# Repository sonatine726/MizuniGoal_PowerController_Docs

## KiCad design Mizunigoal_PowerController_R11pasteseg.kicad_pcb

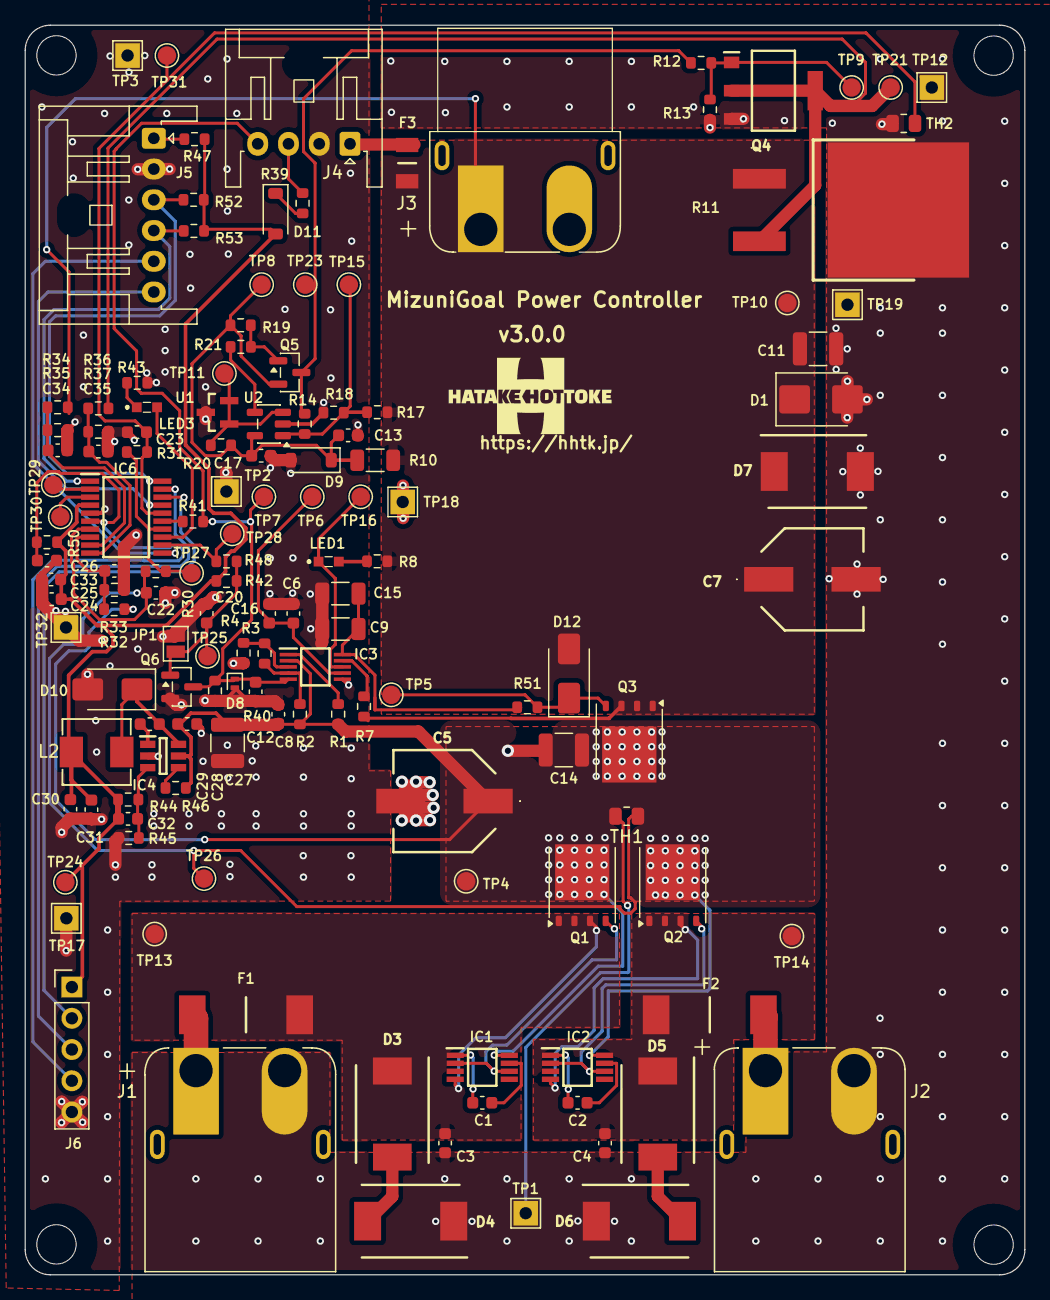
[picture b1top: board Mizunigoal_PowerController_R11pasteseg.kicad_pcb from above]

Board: 2 copper layers, 81.3 x 101.6 mm, 142 parts (0 on the bottom side), 62 nets.

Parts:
C1, C2, C13, C17, C24: 1µF; C_0603_1608Metric
C3, C4: 100pF(C0G/100V); C_0603_1608Metric
C5, C7: 47uF(EEH-ZC1H470P); EEHZA1H680P
C6: 0.33uF; C_0603_1608Metric
C8, C28: 100nF(100V); C_0603_1608Metric
C9, C15: 22nF(C0G/100V/1206); C_1206_3216Metric
C11: 1uF(100V/1210); C_1210_3225Metric
C12, C20, C25, C26, C29, C31, C33: 100nF; C_0603_1608Metric
C14: 4.7µF(100V/1210); C_1210_3225Metric
C16: 0.15uF; C_0603_1608Metric
C22, C23: 10nF; C_0603_1608Metric
C27: 2.2µF(100V/1210); C_1210_3225Metric
C30: 22µF(16V); C_0603_1608Metric
C32: 22pF; C_0603_1608Metric
C34, C35: 1nF(C0G); C_0603_1608Metric
D1: ES2D; D_SMB
D3, D5, D7: SMCJ33A; DIOM7959X262N
D4, D6: SMCJ6.0A; DIOM7959X262N
D8: ESD(5V); D_SOD-882
D9: BZT52C12(12V); D_SOD-123
D10: SS210(100V); D_SMA
D11: BAT46W; D_SOD-123
D12: SMAJ15A; D_SMA
F1, F2: 0456030.ER; FUSC10130X305N
F3: 1206L010_60; FUSC3216X125N
H2, H2#2, H2#3, H2#4: MountingHole_3.2mm_M3_with_safearea
IC1, IC2: LM74610QDGKRQ1; SOP65P490X110-8N
IC3: LM5060MM; SOP50P490X110-10N
IC4: LMR16006XDDCR; SOT95P280X110-6N
IC6: STM32C011F4P6; SOP65P640X120-20N
J1: Conn_01x02_Pin; XT60PW-M-Wide
J2: Conn_01x02_Pin; XT60PW-M-Wide_mod_2
J3: Conn_01x02_Pin; XT60PW-F-Wide
J4: Conn_01x04_Pin; JST_XA_S04B-XASK-1_1x04_P2.50mm_Horizontal
J5: Conn_01x06_Pin; JST_XA_S06B-XASK-1_1x06_P2.50mm_Horizontal
J6: Conn_01x05_Pin; PinHeader_1x05_P2.54mm_Vertical
JP1: Jumper_2_Open; SolderJumper-2_P1.3mm_Open_Pad1.0x1.5mm
L2: 33μH; IND-SMD_L5.4-W5.2
LED1, LED3: SML-D13FWT86; SMLD15YWT86
Q1, Q2, Q3: CSD18540Q5B; TDSON-8-1
Q4: FDT3612; SOT230P700X180-4N
Q5: MMBT3906; SOT-23
Q6: BSS138; SOT-23
R1, R12, R18, R19, R41, R50: 10kΩ; R_0603_1608Metric
R2: 200kΩ; R_0603_1608Metric
R3: 5.76kΩ; R_0603_1608Metric
R4: 13.3kΩ; R_0603_1608Metric
R7: 1kΩ; R_0603_1608Metric
R8: 27kΩ; R_0603_1608Metric
R10: 3.3kΩ(1206); R_1206_3216Metric
R11: TPAN0263F200RK9(200Ω); D2PAK_L10.1-W7.8-P5.08-LS15.3
R13, R33, R35, R37, R44, R46: 100kΩ; R_0603_1608Metric
R14, R32, R34, R36, R42: 1MΩ; R_0603_1608Metric
R17: 118kΩ; R_0603_1608Metric
R20: 6.8kΩ; R_0603_1608Metric
R21: 22kΩ; R_0603_1608Metric
R30, R31: 2.0kΩ; R_0603_1608Metric
R39, R48: 220Ω; R_0603_1608Metric
R40, R52, R53: 2.2kΩ; R_0603_1608Metric
R43: 470Ω; R_0603_1608Metric
R45: 30.1kΩ; R_0603_1608Metric
R47: 0Ω; R_0603_1608Metric
R51: 100Ω; R_0603_1608Metric
TH1, TH2: NCP21XV103J03RA(10kΩ); R_0805_2012Metric
TP1, TP2, TP3, TP12, TP17, TP18, TP19, TP32: GND; TestPoint_THTPad_2.0x2.0mm_Drill1.0mm
TP4: VBUS; TestPoint_Pad_D1.5mm
TP5: Q3_Gate; TestPoint_Pad_D1.5mm
TP6: TIMER; TestPoint_Pad_D1.5mm
TP7: EN; TestPoint_Pad_D1.5mm
TP8: 12V; TestPoint_Pad_D1.5mm
TP9: Q4_Gate; TestPoint_Pad_D1.5mm
TP10: Vout; TestPoint_Pad_D1.5mm
TP11: VREF; TestPoint_Pad_D1.5mm
TP13: Battery_1; TestPoint_Pad_D1.5mm
TP14: Battery_2; TestPoint_Pad_D1.5mm
TP15: Chopper_Sense; TestPoint_Pad_D1.5mm
TP16: NPGD; TestPoint_Pad_D1.5mm
TP21: ChopperLoad; TestPoint_Pad_D1.5mm
TP23: Chopper_Sig; TestPoint_Pad_D1.5mm
TP24: +3V3; TestPoint_Pad_D1.5mm
TP25: EN_GATE; TestPoint_Pad_D1.5mm
TP26: TH1_SENSE; TestPoint_Pad_D1.5mm
TP27: NTC_DRV; TestPoint_Pad_D1.5mm
TP28: SHDN_REQ; TestPoint_Pad_D1.5mm
TP29: MCU_SPARE1; TestPoint_Pad_D1.5mm
TP30: MCU_SPARE2; TestPoint_Pad_D1.5mm
TP31: TH2_SENSE; TestPoint_Pad_D1.5mm
U1: TL431BIDBZR; DBZ0003A_N__mod
U2: LM397; SOT-23-5

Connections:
/3.3V Power/+3V3: C24.1, C25.1, C30.1, C31.1, C32.1, D11.2 (A), IC6.4 (VDD/VDDA), J6.1, L2.1, R42.1, R44.2, R47.2, R50.1, R52.1, R53.1, TP24.1 (1_1)
/Battery1_Fused_1: C3.1, D3.1 (K), F1.2, IC1.4 (ANODE), Q1.1 (S), Q1.2 (S), Q1.3 (S), TP13.1 (1_1)
/Battery1_Fused_2: D3.2 (A), D4.2 (A)
/Battery1_Raw: F1.1, J1.1
/Battery2_Fused_1: C4.1, D5.1 (K), F2.2, IC2.4 (ANODE), Q2.1 (S), Q2.2 (S), Q2.3 (S), TP14.1 (1_1)
/Battery2_Fused_2: D5.2 (A), D6.2 (A)
/Battery2_Raw: F2.1, J2.1
/ChopperLoad: Q4.2 (D_1), Q4.4 (D_2), R11.3, R36.2, TP21.1 (1_1)
/Chopper_12V: C13.1, C17.1, D9.1 (K), Q5.2 (E), R10.2, R19.1, R20.1, TP8.1 (1_1), U2.5 (V+)
/Chopper_Sense: R14.2, R17.2, R18.1, TP15.1 (1_1), U2.1 (-)
/Chopper_Sig: Q5.3 (C), R12.2, R14.1, TP23.1 (1_1)
/Chopper_SigBase: Q5.1 (B), R19.2, R21.1
/EN_SWITCH: J4.3, R39.2
/EN_control/EN: C12.1, D8.1 (K), IC3.5 (EN), J4.4, Q6.3 (D), R40.2, R41.1, TP7.1 (1_1)
/EN_control/EN_GATE: C20.1, JP1.2 (B), Q6.1 (G), R42.2, R48.1, TP25.1 (1_1)
/EN_control/EN_control_MCU/CHOP_SENSE: C35.1, IC6.10 (PA3), R36.1, R37.2
/EN_control/EN_control_MCU/EN_FB: IC6.15 (PA8), R41.2
/EN_control/EN_control_MCU/EXT_ADC1: IC6.11 (PA4), J5.5
/EN_control/EN_control_MCU/EXT_GPIO: IC6.17 (PA12[PA10]), J5.6
/EN_control/EN_control_MCU/I2C_SCL: IC6.20 (PB6), J5.3, R52.2
/EN_control/EN_control_MCU/I2C_SDA: IC6.1 (PB7), J5.4, R53.2
/EN_control/EN_control_MCU/MCU_NRST: C26.1, IC6.6 (PF2-NRST), J6.4, R50.2
/EN_control/EN_control_MCU/MCU_SPARE1: IC6.2 (PC14-OSCX_IN), TP29.1 (1_1)
/EN_control/EN_control_MCU/MCU_SPARE2: IC6.3 (PC15-OSCX_OUT), TP30.1 (1_1)
/EN_control/EN_control_MCU/NTC_DRV: IC6.14 (PA7), R30.2, R31.2, TP27.1 (1_1)
/EN_control/EN_control_MCU/SHDN_REQ: IC6.12 (PA5), R48.2, TP28.1 (1_1)
/EN_control/EN_control_MCU/SWCLK: IC6.19 (PA14-BOOT0), J6.3
/EN_control/EN_control_MCU/SWDIO: IC6.18 (PA13), J6.2
/EN_control/EN_control_MCU/TH1_SENSE: C22.1, IC6.7 (PA0), R30.1, TH1.1, TP26.1 (1_1)
/EN_control/EN_control_MCU/TH2_SENSE: C23.1, IC6.16 (PA11[PA9]), R31.1, TH2.1, TP31.1 (1_1)
/EN_control/EN_control_MCU/VBUS_SENSE: C33.1, IC6.8 (PA1), R32.1, R33.2
/EN_control/EN_control_MCU/VOUT_SENSE: C34.1, IC6.9 (PA2), R34.1, R35.2
/Gate_HV_1: D12.1 (A1), Q3.4 (G), R51.1, TP5.1 (1_1)
/Gate_HV_2: Q4.1 (G), R12.1, R13.1, TP9.1 (1_1)
/IC3_OUT: IC3.9 (OUT), R7.2
/IdealDiode_gate_1: IC1.2 (GATE_PULL_DOWN), IC1.6 (GATE_DRIVE), Q1.4 (G)
/IdealDiode_gate_2: IC2.2 (GATE_PULL_DOWN), IC2.6 (GATE_DRIVE), Q2.4 (G)
/IdealDiode_vcap_1: C1.2, IC1.7 (VCAPH)
/IdealDiode_vcap_2: C1.1, IC1.1 (VCAPL)
/IdealDiode_vcap_3: C2.2, IC2.7 (VCAPH)
/IdealDiode_vcap_4: C2.1, IC2.1 (VCAPL)
/NPGD: IC3.8 (NPGD), LED1.1 (K), TP16.1 (1_1)
/OVP: IC3.3 (OVP), R3.2, R4.1
/SENSE: IC3.1 (SENSE), R1.2
/TIMER: C6.1, C16.1, IC3.7 (TIMER), TP6.1 (1_1)
/UVLO: IC3.4 (UVLO), R2.2, R3.1
/VBUS: C5.1 (+), C8.1, C14.1, C27.1, C28.1, IC1.8 (CATHODE), IC2.8 (CATHODE), IC3.2 (VIN), IC4.5 (VIN), Q1.5 (D), Q2.5 (D), Q3.5 (D), R1.1, R2.1, R32.2, R46.1, TP4.1 (1_1)
/VREF: R20.2, TP11.1 (1_1), U1.1, U1.2, U2.3 (+)
/Vout: C7.1 (+), C11.1, D1.1 (K), D7.1 (K), D12.2 (A2), F3.1, J3.1, Q3.1 (S), Q3.2 (S), Q3.3 (S), R7.1, R8.1, R10.1, R11.1, R17.1, R34.2, TP10.1 (1_1)
/Vout_after_PPTC: F3.2, J4.1
GND: C3.2, C4.2, C5.2 (-), C6.2, C7.2 (-), C8.2, C9.2, C11.2, C12.2, C13.2, C14.2, C15.2, C16.2, C17.2, C20.2, C22.2, C23.2, C24.2, C25.2, C26.2, C27.2, C28.2, C30.2, C31.2, C33.2, C34.2, C35.2, D1.2 (A), D4.1 (K), D6.1 (K), D7.2 (A), D8.2 (A), D9.2 (A), D10.2 (A), IC3.6 (GND), IC4.2 (GND), IC6.5 (VSS/VSSA), J1.2, J2.2, J3.2, J4.2, J5.2, J6.5, JP1.1 (A), Q4.3 (S), Q6.2 (S), R4.2, R11.2, R13.2, R18.2, R33.1, R35.1, R37.1, R40.1, R43.1, R45.1, TH1.2, TH2.2, TP1.1 (1_1), TP2.1 (1_1), TP3.1 (1_1), TP12.1 (1_1), TP17.1 (1_1), TP18.1 (1_1), TP19.1 (1_1), TP32.1 (1_1), U1.3, U2.2 (V-)
unnamed: C29.1, D10.1 (K), IC4.6 (SW), L2.2
unnamed: D11.1 (K), R39.1
unnamed: C9.1, C15.1, IC3.10 (GATE), R51.2
unnamed: C29.2, IC4.1 (CB)
unnamed: C32.2, IC4.3 (FB), R44.1, R45.2
unnamed: IC4.4 (~SHDN), R46.2
unnamed: IC6.13 (PA6), LED3.2 (A)
unnamed: J5.1, R47.1
unnamed: LED1.2 (A), R8.2
unnamed: LED3.1 (K), R43.2
unnamed: R21.2, U2.4

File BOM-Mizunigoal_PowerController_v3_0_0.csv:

Comment,Designator,Footprint,LCSC,Quantity
0.15uF,C16,C_0603_1608Metric,C513735,1
0.33uF,C6,C_0603_1608Metric,C282682,1
0456030.ER,"F1,F2",FUSC10130X305N,C187558,2
0Ω,R47,R_0603_1608Metric,C21189,1
100kΩ,"R13,R33,R35,R37,R44,R46",R_0603_1608Metric,C25803,6
100nF,"C12,C20,C25,C26,C29,C31,C33",C_0603_1608Metric,C14663,7
100nF(100V),"C28,C8",C_0603_1608Metric,C15725,2
100pF(C0G/100V),"C3,C4",C_0603_1608Metric,C44567,2
100Ω,R51,R_0603_1608Metric,C22775,1
10kΩ,"R1,R12,R18,R19,R41,R50",R_0603_1608Metric,C25804,6
10nF,"C22,C23",C_0603_1608Metric,C57112,2
118kΩ,R17,R_0603_1608Metric,C5126230,1
1206L010_60,F3,FUSC3216X125N,C18198325,1
13.3kΩ,R4,R_0603_1608Metric,C25952,1
1MΩ,"R14,R32,R34,R36,R42",R_0603_1608Metric,C22935,5
1kΩ,R7,R_0603_1608Metric,C21190,1
1nF(C0G),"C34,C35",C_0603_1608Metric,C163508,2
1uF(100V/1210),C11,C_1210_3225Metric,C24365,1
1µF,"C1,C13,C17,C2,C24",C_0603_1608Metric,C15849,5
2.0kΩ,"R30,R31",R_0603_1608Metric,C22975,2
2.2kΩ,"R40,R52,R53",R_0603_1608Metric,C4190,3
2.2µF(100V/1210),C27,C_1210_3225Metric,C153036,1
200kΩ,R2,R_0603_1608Metric,C25811,1
220Ω,"R39,R48",R_0603_1608Metric,C22962,2
22kΩ,R21,R_0603_1608Metric,C31850,1
22nF(C0G/100V/1206),"C15,C9",C_1206_3216Metric,C711005,2
22pF,C32,C_0603_1608Metric,C1653,1
22µF(16V),C30,C_0603_1608Metric,C22367828,1
27kΩ,R8,R_0603_1608Metric,C22967,1
3.3kΩ(1206),R10,R_1206_3216Metric,C26032,1
30.1kΩ,R45,R_0603_1608Metric,C23000,1
33μH,L2,IND-SMD_L5.4-W5.2,C41413117,1
4.7µF(100V/1210),C14,C_1210_3225Metric,C381466,1
470Ω,R43,R_0603_1608Metric,C23179,1
47uF(EEH-ZC1H470P),"C5,C7",EEHZA1H680P,C454346,2
5.76kΩ,R3,R_0603_1608Metric,C23070,1
6.8kΩ,R20,R_0603_1608Metric,C23212,1
BAT46W,D11,D_SOD-123,C7420332,1
BSS138,Q6,SOT-23,C7420339,1
BZT52C12(12V),D9,D_SOD-123,C20622487,1
BSC028N06NS,"Q1,Q2,Q3",TDSON-8-1,C148250,3
Conn_01x04_Pin,J4,JST_XA_S04B-XASK-1_1x04_P2.50mm_Horizontal,C161668,1
Conn_01x06_Pin,J5,JST_XA_S06B-XASK-1_1x06_P2.50mm_Horizontal,C491715,1
ES2D,D1,D_SMB,C232831,1
ESD(5V),D8,D_SOD-882,C85402,1
FDT3612,Q4,SOT230P700X180-4N,C20617897,1
LM397,U2,SOT-23-5,C132076,1
LM5060MM,IC3,SOP50P490X110-10N,C74456,1
LM74610QDGKRQ1,"IC1,IC2",SOP65P490X110-8N,C2649431,2
LMR16006XDDCR,IC4,SOT95P280X110-6N,C87080,1
MMBT3906,Q5,SOT-23,C7420354,1
NCP21XV103J03RA(10kΩ),"TH1,TH2",R_0805_2012Metric,C113141,2
SMAJ15A,D12,D_SMA,C19077535,1
SMCJ33A,"D3,D5,D7",DIOM7959X262N,C42371548,3
SMCJ6.0A,"D4,D6",DIOM7959X262N,C42394420,2
SML-D13FWT86,"LED1,LED3",SMLD15YWT86,C459722,2
SS210(100V),D10,D_SMA,C14996,1
STM32C011F4P6,IC6,SOP65P640X120-20N,C5452432,1
TL431BIDBZR,U1,DBZ0003A_N__mod,C41283,1
TPAN0263F200RK9(200Ω),R11,D2PAK_L10.1-W7.8-P5.08-LS15.3,C39097133,1
PZ254V-11-05P,J6,PinHeader_1x05_P2.54mm_Vertical,C492404,1
Jumper_2_Open,JP1,SolderJumper-2_P1.3mm_Open_Pad1.0x1.5mm,,1
